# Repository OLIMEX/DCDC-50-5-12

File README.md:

# DCDC-50-5-12
Industrial grade -40+85C power supply module for OLinuXino. Suitrable also for 12 and 24V car battery systems.

## Features

* Input voltage 8-50VDC
* Output voltage 5V/1.5A or 12V/1.5A
* Dimensions: 50x35x15mm

## Licenses

* Hardware is released under CERN Open Hardware Licence Version 2 - Strongly Reciprocal, all silkscreen credits to Olimex should remain;
* Software is released under GPL3 Licensee
* Documentation is released under CC BY-SA 4.0

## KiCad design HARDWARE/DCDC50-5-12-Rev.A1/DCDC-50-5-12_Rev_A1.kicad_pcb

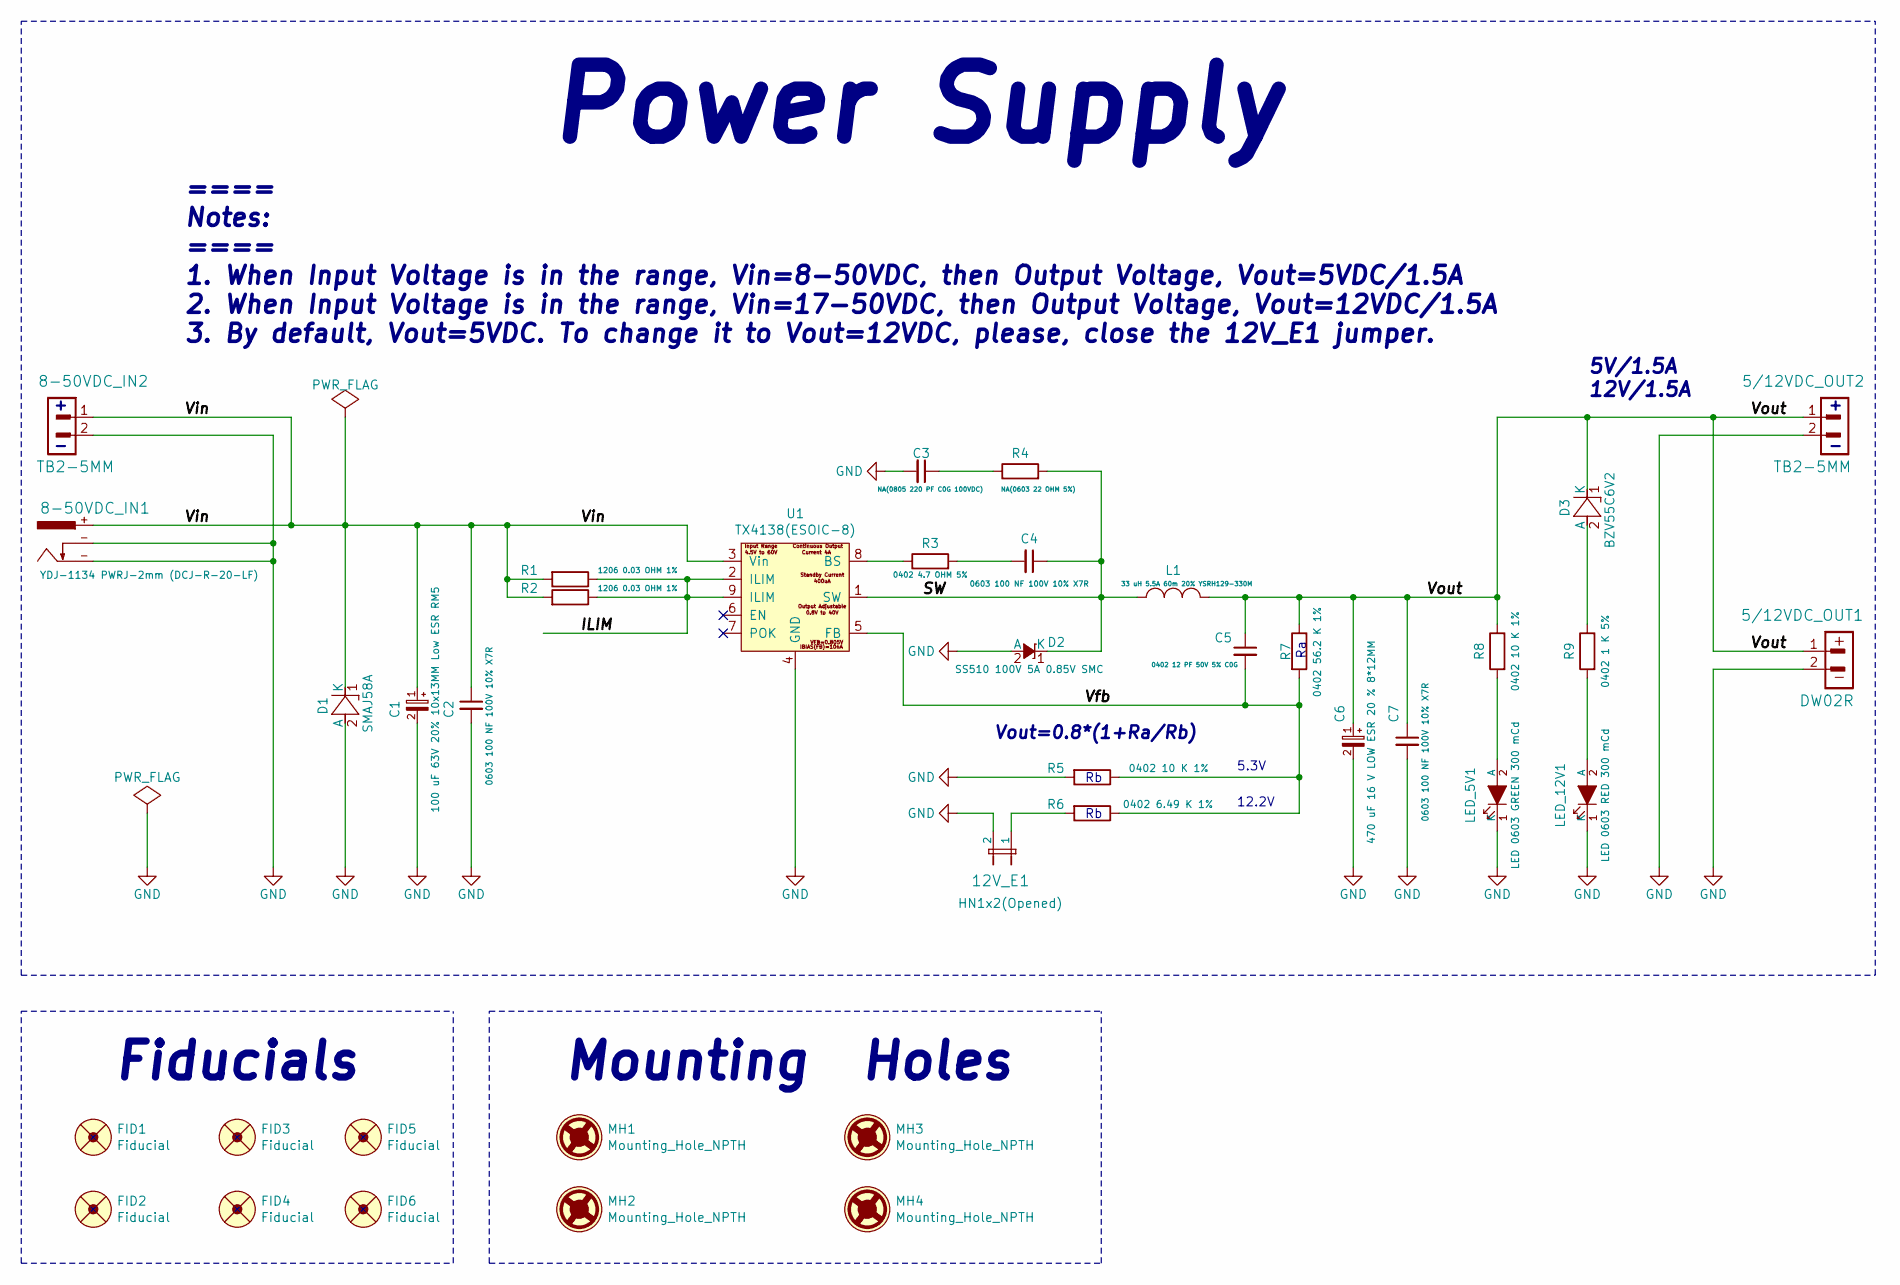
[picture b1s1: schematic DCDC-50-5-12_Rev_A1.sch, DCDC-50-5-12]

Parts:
5/12VDC_OUT1: DW02R; LIPO_BAT-CON2DW02R
5/12VDC_OUT2, 8-50VDC_IN2: TB2-5MM; TB2-5mm
8-50VDC_IN1: YDJ-1134 PWRJ-2mm (DCJ-R-20-LF); PWRJ-2mm(YDJ-1134)
12V_E1: HN1x2(Opened); HN1x2_Jumper
C1: 100 uF 63V 20% 10x13MM Low ESR RM5; CPOL-RM5mm_10.0x16.0mm_PTH
C2, C4, C7: 0603 100 NF 100V 10% X7R; C_0603_5MIL_DWS
C3: NA(0805 220 PF C0G 100VDC); C_0805_5MIL_DWS
C5: 0402 12 PF 50V 5% C0G; C_0402_5MIL_DWS
C6: 470 uF 16 V LOW ESR 20 % 8*12MM; CPOL-RM3.5mm_8.0x11.5mm_PTH
D1: SMAJ58A; SMA-KA
D2: SS510 100V 5A 0.85V SMC; DO214AB(SMC)_1(K)-2(A)
D3: BZV55C6V2; SOD80C-4148-KA
FID1, FID2, FID3, FID4, FID5, FID6: Fiducial; Fiducial1x3
L1: 33 uH 5.5A 60m 20% YSRH129-330M; HSMRH129_12.0x12.5x9.5(max)
LED_5V1: LED 0603 GREEN 300 mCd; LED_0603_KA
LED_12V1: LED 0603 RED 300 mCd; LED_0603_KA
MH1, MH2, MH3, MH4: Mounting_Hole_NPTH; Mounting_Hole_Drill-3.3mm_Clerance-7mm
R1, R2: 1206 0.03 OHM 1%; R_1206_5MIL_DWS
R3: 0402 4.7 OHM 5%; R_0402_5MIL_DWS
R4: NA(0603 22 OHM 5%); R_0603_5MIL_DWS
R5, R8: 0402 10 K 1%; R_0402_5MIL_DWS
R6: 0402 6.49 K 1%; R_0402_5MIL_DWS
R7: 0402 56.2 K 1%; R_0402_5MIL_DWS
R9: 0402 1 K 5%; R_0402_5MIL_DWS
U1: TX4138(ESOIC-8); ESOIC-8

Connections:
/ILIM: R1.1, R2.1, U1.2 (ILIM), U1.9 (ILIM)
/SW: C4.1, D2.1 (K), L1.1, R4.2, U1.1 (SW)
/Vfb: C5.2, R5.1, R6.1, R7.2, U1.5 (FB)
/Vin: 8-50VDC_IN1.+, 8-50VDC_IN2.1, C1.1 (+), C2.1, D1.1 (K), R1.2, R2.2, U1.3 (Vin)
/Vout: 5/12VDC_OUT1.1, 5/12VDC_OUT2.1, C5.1, C6.1 (+), C7.1, D3.1 (K), L1.2, R7.1, R8.1
GND: 5/12VDC_OUT1.2, 5/12VDC_OUT2.2, 8-50VDC_IN1.-, 8-50VDC_IN2.2, 12V_E1.2, C1.2 (-), C2.2, C3.2, C6.2 (-), C7.2, D1.2 (A), D2.2 (A), LED_5V1.1 (K), LED_12V1.1 (K), R5.2, U1.4 (GND)
unnamed: 12V_E1.1, R6.2
unnamed: C3.1, R4.1
unnamed: C4.2, R3.2
unnamed: D3.2 (A), R9.1
unnamed: LED_5V1.2 (A), R8.2
unnamed: LED_12V1.2 (A), R9.2
unnamed: R3.1, U1.8 (BS)

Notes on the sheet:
Fiducials
Vout=0.8*(1+Ra/Rb)
Mounting Holes
==== Notes: ==== 1. When Input Voltage is in the range, Vin=8-50VDC, then Output Voltage, Vout=5VDC/1.5A 2. When Input Voltage is in the range, Vin=17-50VDC, then Output Voltage, Vout=12VDC/1.5A 3. By default, Vout=5VDC. To change it to Vout=12VDC, please, close the 12V_E1 jumper.
Power Supply
5.3V
12.2V
5V/1.5A 12V/1.5A

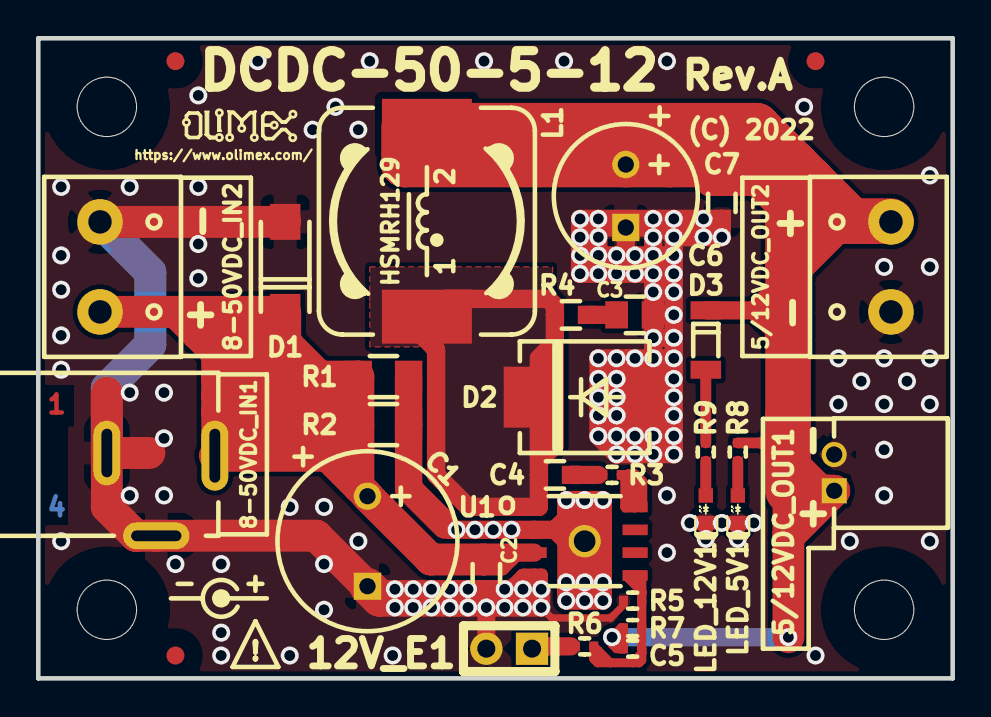
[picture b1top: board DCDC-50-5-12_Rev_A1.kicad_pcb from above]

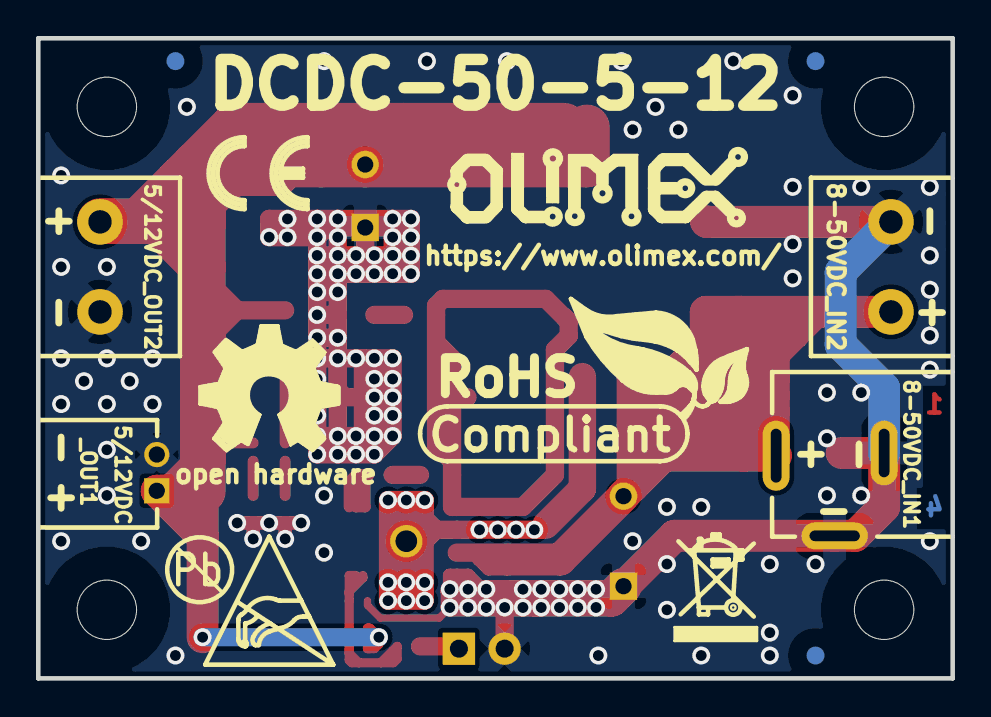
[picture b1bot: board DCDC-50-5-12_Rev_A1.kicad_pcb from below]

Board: 4 copper layers, 50.8 x 35.6 mm, 46 parts (10 on the bottom side), 13 nets.

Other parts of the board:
Logo_OLIMEX_SMALL_TB: Logo_OLIMEX_SMALL_TB
Logo_OSHW: LOGO_OPENHARDWARE_8x8
Logo_Olimex: OLIMEX_LOGO_TB
Sign_Antistatic: Val**; LOGO_ANTISTATIC_1
Sign_CE: CE_Sign
Sign_PB-Free: Sign_PB-Free
Sign_RecycleBin: LOGO_RECYCLEBIN_1
Sign_RoHS_1: Sign_RoHS_1

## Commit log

2024-02-16 initial upload

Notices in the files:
HARDWARE/DCDC50-5-12-Rev.A1/DCDC-50-5-12_Rev_A1.kicad_pcb:
(C) 2022
